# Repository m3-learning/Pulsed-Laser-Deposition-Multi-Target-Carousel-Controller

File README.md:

# Pulsed-Laser-Deposition-Multi-Target-Carousel-Controller

Open source multi-target carousel controller for Neccera PLD System

Created by: The M3 Learning Group

All designs and code by: Ryan Forelli

## Components needed for PCB assembly
-   1x Custom PCB
-   2x A4988 stepper motor drivers
-   1x ATmega328P AVR microcontroller
-   5x 5mm DIP LEDs
-   1x Pin header set
-   1x [Molex 6 Circuit Wire Connector][1]
-   1x through hole pushbutton
-   1x 16 MHz crystal oscillator
-   2x 22pF ceramic capacitors
-   1x 10uF electrolytic capacitor
-   1x 100uF electrolytic capacitor
-   1x 10k through-hole resistor
-   1x Assorted single-core jumper wires
-   1x [Standoffs][0] (optional)
-   1x Custom back plate (optional)
-   1x [USB to TTL Adapter][2]

## Installation Notes
-   Supply PCB with 5V supply from USB to TTL Adapter
-   Supply Stepper motor controller with 24V from Multi-Target Carousel Controller or other source
-   Only four Molex connector pins are used. Use PCB schematic for reference when wiring connectors to PCB

## Usage Instructions
-   Power PLD Controller module
-   Open LabVIEW pldsyscontrol.exe and run the Virtual Instrument (VI)
-   Select COM port
-   Home raster motor (does not home to a specific target)
-   Select target and begin use

[0]: https://www.amazon.com/Csdtylh-Male-Female-Standoff-Stainless-Assortment/dp/B06Y5TJXY1/ref=sr_1_3?dchild=1&keywords=standoff&qid=1620104015&sr=8-3
[1]: https://www.amazon.com/gp/product/B074M15FS1/ref=ppx_yo_dt_b_asin_title_o02_s00?ie=UTF8&psc=1
[2]: https://www.amazon.com/DSD-TECH-SH-U09C2-Debugging-Programming/dp/B07TXVRQ7V/ref=sr_1_8?dchild=1&keywords=FT232RL+USB+to+Serial&qid=1616559163&s=electronics&sr=1-8#customerReviews

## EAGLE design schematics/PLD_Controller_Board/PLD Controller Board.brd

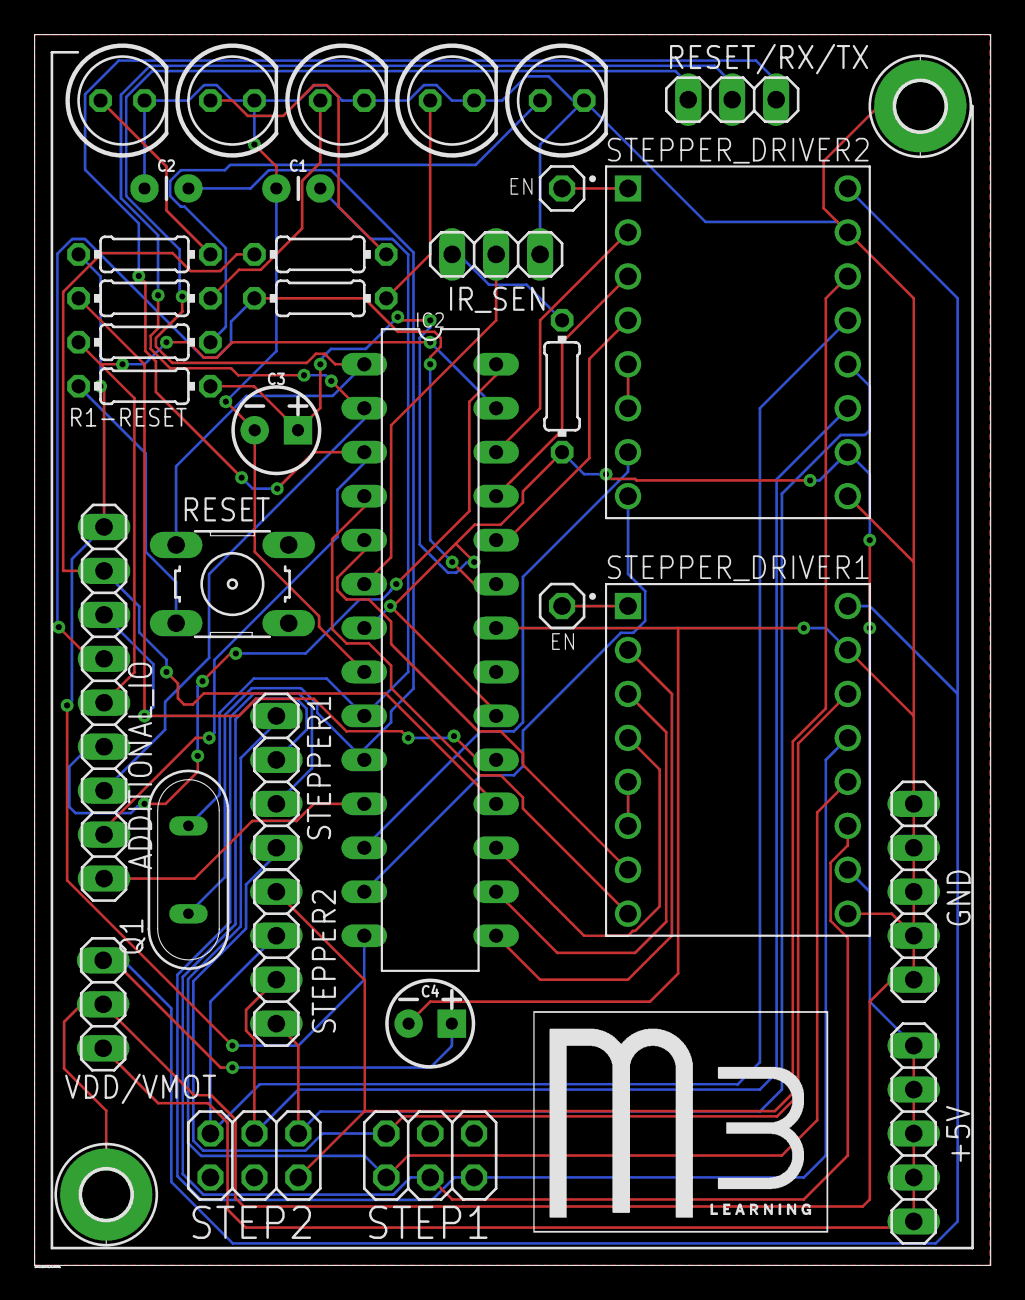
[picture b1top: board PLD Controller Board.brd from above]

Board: 2 copper layers, 55.2 x 71.1 mm, 35 parts (0 on the bottom side), 45 nets.

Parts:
+5V: 1X05
ADDITIONAL_IO: 1X09
C1, C2: 22pF; CAP-PTH-2.54
C3: 10uF; CPOL-RADIAL-2.5MM-5MM
C4: 100uF; CPOL-RADIAL-2.5MM-5MM
ENABLE1, ENABLE2: 1X01
GND: 1X05
H1, H2: MOUNT-PAD-ROUND2.8; 2,8-PAD
IC2: ATMEGA328-PU; DIL28
IR_SEN: 1X03
LED1, LED2, LED3, LED4, LED5: LED5MM
Q1: QS
R1, R2, R3, R4, R5: 220; 0204/7
R1-RESET, R2-SENSOR: 10K; 0204/7
RESET: B3F-10XX
RESET/RX/TX: 1X03
STEPPER1, STEPPER2: 1X04
STEPPER1_C, STEPPER2_C: 2X03
STEPPER_DRIVER1, STEPPER_DRIVER2: A4988_STEPPER_DRIVER; MODULE_A4988_STEPPER_MOTOR_DRIVER_CARRIER
VDD/VMOT: 1X03

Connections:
+5V: C3.1, GND.1, GND.2, GND.3, GND.4, GND.5, IC2.7, IC2.20, R1-RESET.1, R2-SENSOR.2, STEPPER_DRIVER1.10, STEPPER_DRIVER2.10, VDD/VMOT.3
+24V: C4.1, STEPPER_DRIVER1.16, STEPPER_DRIVER2.16, VDD/VMOT.1
GND: +5V.1, +5V.2, +5V.3, +5V.4, +5V.5, C1.1, C2.1, C3.2, C4.2, H1.B2,8, H2.B2,8, IC2.8, IC2.22, IR_SEN.1, LED1.K, LED2.K, LED3.K, LED4.K, LED5.K, STEPPER_DRIVER1.9, STEPPER_DRIVER1.15, STEPPER_DRIVER2.9, STEPPER_DRIVER2.15, VDD/VMOT.2
unnamed: IC2.1, RESET.1, RESET/RX/TX.1
unnamed: C1.2, IC2.9, Q1.2
unnamed: C2.2, IC2.10, Q1.1
unnamed: R1-RESET.2, RESET.3
unnamed: STEPPER_DRIVER1.5, STEPPER_DRIVER1.6
unnamed: STEPPER_DRIVER2.5, STEPPER_DRIVER2.6
unnamed: IR_SEN.3, R2-SENSOR.1
unnamed: STEPPER1.2, STEPPER1_C.4, STEPPER_DRIVER1.11
unnamed: STEPPER1.3, STEPPER1_C.2, STEPPER_DRIVER1.13
unnamed: STEPPER1.4, STEPPER1_C.5, STEPPER_DRIVER1.14
unnamed: STEPPER2.1, STEPPER2_C.6, STEPPER_DRIVER2.12
unnamed: STEPPER2.2, STEPPER2_C.4, STEPPER_DRIVER2.11
unnamed: STEPPER2.3, STEPPER2_C.2, STEPPER_DRIVER2.13
unnamed: STEPPER2.4, STEPPER2_C.5, STEPPER_DRIVER2.14
unnamed: ENABLE1.1, STEPPER_DRIVER1.1
unnamed: ENABLE2.1, STEPPER_DRIVER2.1
unnamed: LED4.A, R4.2
unnamed: LED3.A, R3.2
unnamed: LED2.A, R2.2
unnamed: LED1.A, R1.2
unnamed: IC2.4, STEPPER_DRIVER1.8
unnamed: IC2.5, STEPPER_DRIVER1.7
unnamed: IC2.13, STEPPER_DRIVER2.8
unnamed: IC2.12, STEPPER_DRIVER2.7
unnamed: IC2.15, STEPPER_DRIVER1.2
unnamed: IC2.16, STEPPER_DRIVER1.3
unnamed: IC2.17, STEPPER_DRIVER1.4
unnamed: IC2.26, STEPPER_DRIVER2.2
unnamed: IC2.25, STEPPER_DRIVER2.3
unnamed: IC2.24, STEPPER_DRIVER2.4
unnamed: IC2.6, IR_SEN.2
unnamed: ADDITIONAL_IO.9, IC2.14, R1.1
unnamed: ADDITIONAL_IO.8, IC2.18, R2.1
unnamed: ADDITIONAL_IO.7, IC2.19, R3.1
unnamed: ADDITIONAL_IO.6, IC2.23, R4.1
unnamed: ADDITIONAL_IO.5, IC2.27, R5.1
unnamed: ADDITIONAL_IO.4, IC2.28
unnamed: ADDITIONAL_IO.3, IC2.2, RESET/RX/TX.2
unnamed: ADDITIONAL_IO.2, IC2.3, RESET/RX/TX.3
unnamed: ADDITIONAL_IO.1, IC2.11
unnamed: LED5.A, R5.2
unnamed: STEPPER1.1, STEPPER1_C.6, STEPPER_DRIVER1.12

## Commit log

2021-06-27 schematic update

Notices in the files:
schematics/PLD_Controller_Board/PLD Controller Board.brd:
Released under BSD-3 License.
parts and their libraries:
SparkFun-Capacitors: Licensing: Creative Commons ShareAlike 4.0 International - https://creativecommons.org/licenses/by-sa/4.0
